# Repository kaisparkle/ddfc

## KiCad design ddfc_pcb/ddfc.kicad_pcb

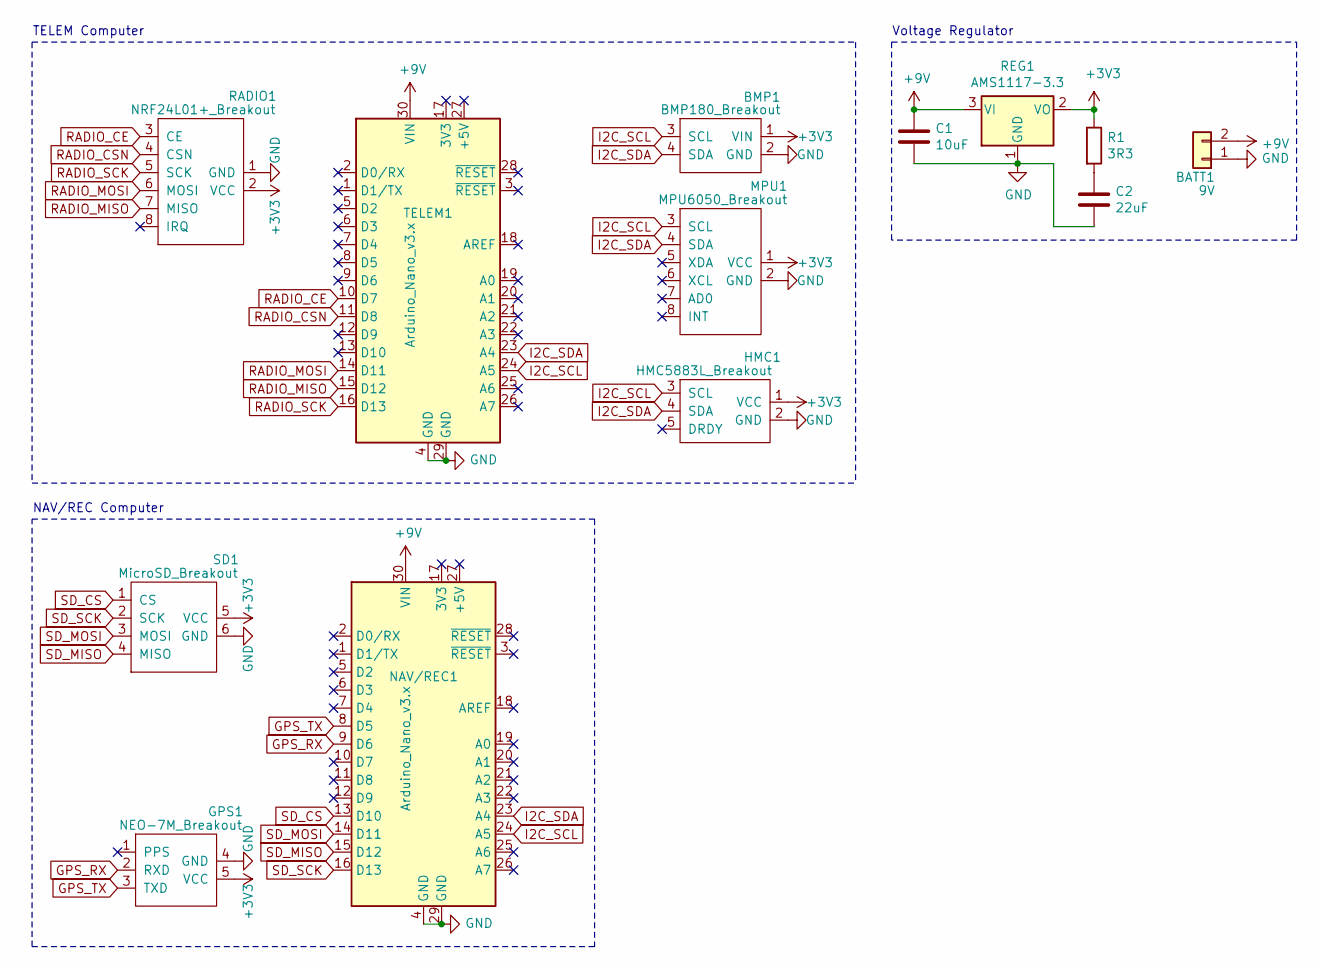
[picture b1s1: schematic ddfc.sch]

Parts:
BATT1: 9V; PinHeader_1x02_P2.54mm_Vertical
BMP1: BMP180_Breakout
C1: 10uF; C_0805_2012Metric_Pad1.18x1.45mm_HandSolder
C2: 22uF; C_0805_2012Metric_Pad1.18x1.45mm_HandSolder
GPS1: NEO-7M_Breakout
HMC1: HMC5883L_Breakout
MPU1: MPU6050_Breakout
NAV/REC1: Arduino_Nano_v3.x; Arduino_Nano_Clone
R1: 3R3; R_0805_2012Metric_Pad1.20x1.40mm_HandSolder
RADIO1: NRF24L01+_Breakout
REG1: AMS1117-3.3; SOT-223-3_TabPin2
SD1: MicroSD_Breakout
TELEM1: Arduino_Nano_v3.x; Arduino_Nano_Clone

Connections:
+3V3: BMP1.1 (VIN), GPS1.5 (VCC), HMC1.1 (VCC), MPU1.1 (VCC), R1.1, RADIO1.2 (VCC), REG1.2 (VO), SD1.5 (VCC)
+9V: BATT1.2, C1.1, NAV/REC1.30 (VIN), REG1.3 (VI), TELEM1.30 (VIN)
GND: BATT1.1, BMP1.2 (GND), C1.2, C2.2, GPS1.4 (GND), HMC1.2 (GND), MPU1.2 (GND), NAV/REC1.4 (GND), NAV/REC1.29 (GND), RADIO1.1 (GND), REG1.1 (GND), SD1.6 (GND), TELEM1.4 (GND), TELEM1.29 (GND)
GPS_RX: GPS1.2 (RXD), NAV/REC1.9 (D6)
GPS_TX: GPS1.3 (TXD), NAV/REC1.8 (D5)
I2C_SCL: BMP1.3 (SCL), HMC1.3 (SCL), MPU1.3 (SCL), NAV/REC1.24 (A5), TELEM1.24 (A5)
I2C_SDA: BMP1.4 (SDA), HMC1.4 (SDA), MPU1.4 (SDA), NAV/REC1.23 (A4), TELEM1.23 (A4)
unnamed: C2.1, R1.2
RADIO_CE: RADIO1.3 (CE), TELEM1.10 (D7)
RADIO_CSN: RADIO1.4 (CSN), TELEM1.11 (D8)
RADIO_MISO: RADIO1.7 (MISO), TELEM1.15 (D12)
RADIO_MOSI: RADIO1.6 (MOSI), TELEM1.14 (D11)
RADIO_SCK: RADIO1.5 (SCK), TELEM1.16 (D13)
SD_CS: NAV/REC1.13 (D10), SD1.1 (CS)
SD_MISO: NAV/REC1.15 (D12), SD1.4 (MISO)
SD_MOSI: NAV/REC1.14 (D11), SD1.3 (MOSI)
SD_SCK: NAV/REC1.16 (D13), SD1.2 (SCK)

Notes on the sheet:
Voltage Regulator
TELEM Computer
NAV/REC Computer

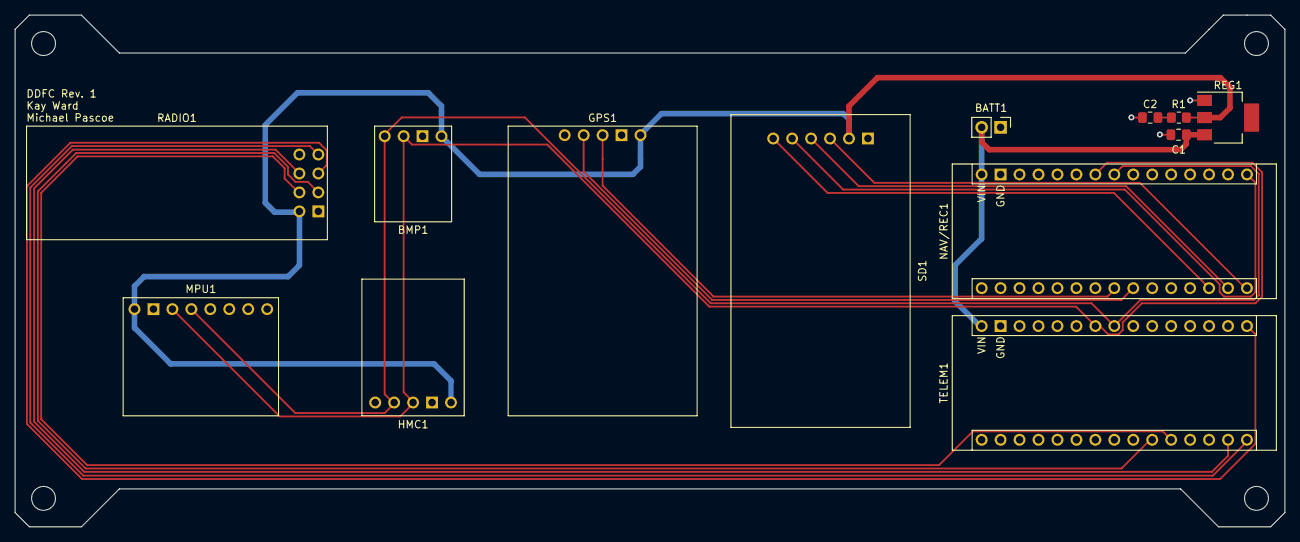
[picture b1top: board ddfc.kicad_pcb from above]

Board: 2 copper layers, 170.2 x 68.6 mm, 17 parts (0 on the bottom side), 17 nets.

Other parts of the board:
HOLE1, HOLE2, HOLE3, HOLE4: MountingHole_3.2mm_M3

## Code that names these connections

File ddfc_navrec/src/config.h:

// Project: ddfc_navrec
// Purpose: Configuration constants for modules

#ifndef CONFIG_H
#define CONFIG_H

// SD module
const uint8_t SD_CS_PIN = 10;

// GPS module
const uint8_t MODULE_GPS_ID = 0x01;
const uint8_t GPS_TX_PIN = 5;
const uint8_t GPS_RX_PIN = 6;
// minimum interval between data fetches in milliseconds
// NEO-7M running at 1Hz
const uint16_t GPS_FETCH_INTERVAL = 1000;
#define GPS_DEBUG true

// I2C
const uint8_t I2C_MASTER_ADDRESS = 1;
const uint8_t I2C_SLAVE_ADDRESS = 2;

#endif

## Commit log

2021-07-26 Initial commit.
2021-07-31 Change packet magic to 2 bytes.
2021-08-04 WIP UBX GPS support, move config defines to own file, WIP arming switch
2021-08-08 Replace constant defines with typed constants, add block comment headers, sync rx and tx NRF code.
2021-08-23 Add support for BMP180, basic ground plotting Python script
2021-09-25 Rename project, add WIP PCB, remove arming module.
2021-10-08 Split into NAVREC and TELEM, implement HMC and MPU modules
2021-10-09 Implement I2C communication and SD logging.
2021-10-09 Add remaining modules and logging to Python script.
2021-10-09 Add packet rate to Python script, increase data rate on TELEM
2021-10-11 Add raw data from Oct. 10 flight.
2021-10-13 Add raw data to CSV script, add converted Oct. 10th flight data.
